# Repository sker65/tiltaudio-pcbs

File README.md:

# tiltaudio-pcbs
PCBs and shields for TILT!Audio, see https://tiltaudio.com

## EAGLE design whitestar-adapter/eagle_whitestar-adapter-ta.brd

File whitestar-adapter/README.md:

# Whitestar Adapter

Small PCB to hook on the main cpu to connect TILT!Audio with Whitestar mainboards

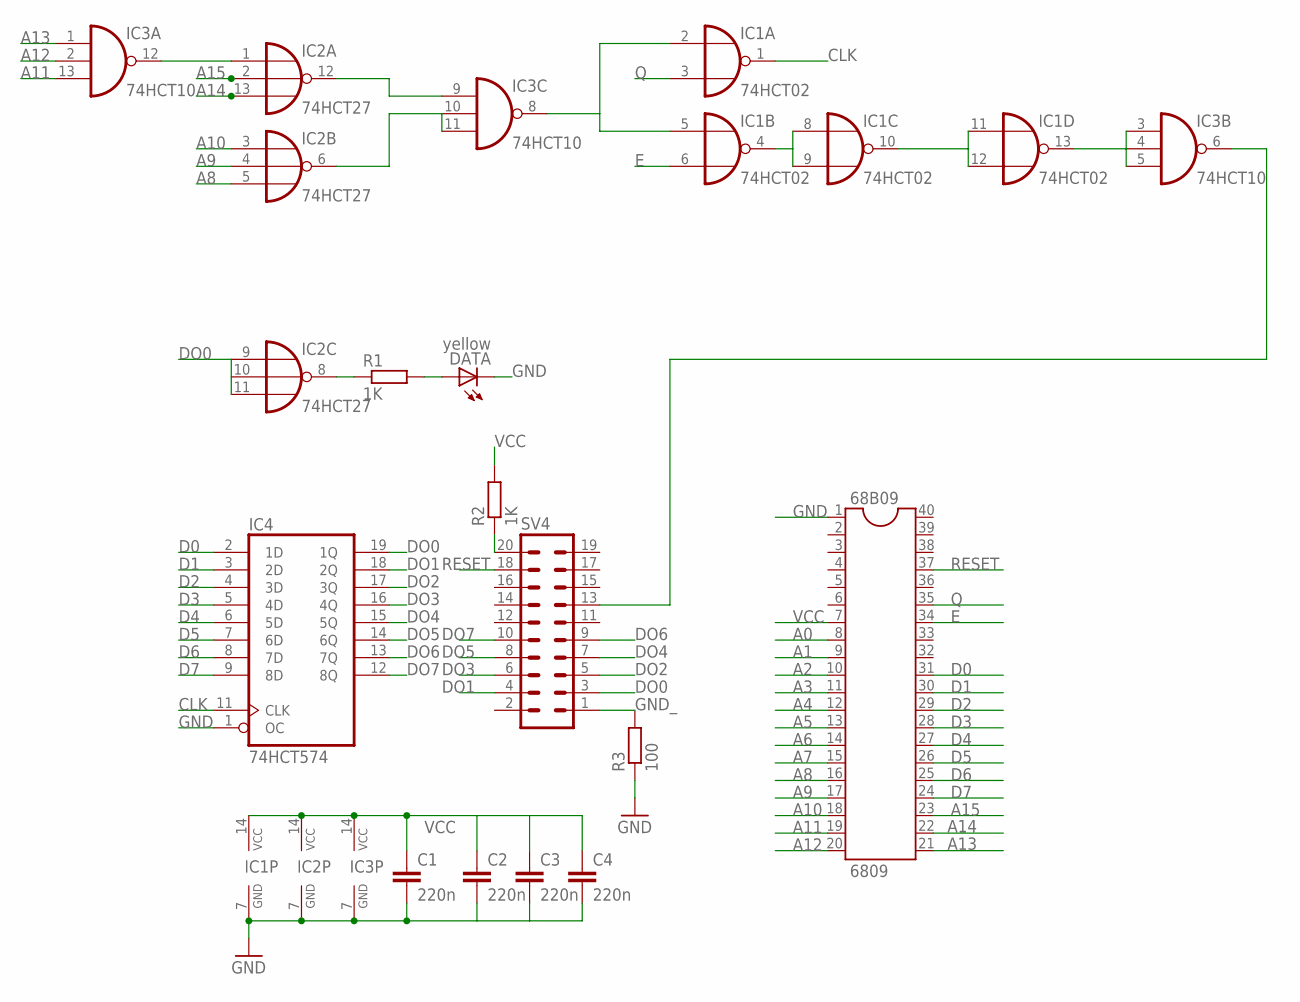
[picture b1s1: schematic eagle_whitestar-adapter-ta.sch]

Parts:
68B09: 6809; DIL40
C1, C2, C3, C4: 220n; C0603K
DATA: yellow; SML0603
IC1: 74HCT02; SO14
IC2: 74HCT27; SO14
IC3: 74HCT10; SO14
IC4: 74HCT574; SO20W
R1, R2: 1K; R0603
R3: 100; R0603
SV4: MA10-2

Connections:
A0: 68B09.8
A1: 68B09.9
A2: 68B09.10
A3: 68B09.11
A4: 68B09.12
A5: 68B09.13
A6: 68B09.14
A7: 68B09.15
A8: 68B09.16, IC2.5 (I2)
A9: 68B09.17, IC2.4 (I1)
A10: 68B09.18, IC2.3 (I0)
A11: 68B09.19, IC3.13 (I2)
A12: 68B09.20, IC3.2 (I1)
A13: 68B09.21, IC3.1 (I0)
A14: 68B09.22, IC2.13 (I2)
A15: 68B09.23, IC2.2 (I1)
CLK: IC1.1 (O), IC4.11 (CLK)
D0: 68B09.31, IC4.2 (1D)
D1: 68B09.30, IC4.3 (2D)
D2: 68B09.29, IC4.4 (3D)
D3: 68B09.28, IC4.5 (4D)
D4: 68B09.27, IC4.6 (5D)
D5: 68B09.26, IC4.7 (6D)
D6: 68B09.25, IC4.8 (7D)
D7: 68B09.24, IC4.9 (8D)
DO0: IC2.9 (I0), IC2.10 (I1), IC2.11 (I2), IC4.19 (1Q), SV4.3
DO1: IC4.18 (2Q), SV4.4
DO2: IC4.17 (3Q), SV4.5
DO3: IC4.16 (4Q), SV4.6
DO4: IC4.15 (5Q), SV4.7
DO5: IC4.14 (6Q), SV4.8
DO6: IC4.13 (7Q), SV4.9
DO7: IC4.12 (8Q), SV4.10
E: 68B09.34, IC1.6 (I1)
GND: 68B09.1, C1.2, C2.2, C3.2, C4.2, DATA.C, IC1.7 (GND), IC2.7 (GND), IC3.7 (GND), IC4.1 (OC), IC4.10 (GND), R3.1
GND_: R3.2, SV4.1
unnamed: IC2.1 (I0), IC3.12 (O)
unnamed: IC2.12 (O), IC3.9 (I0)
unnamed: IC2.6 (O), IC3.10 (I1), IC3.11 (I2)
unnamed: IC1.2 (I0), IC1.5 (I0), IC3.8 (O)
unnamed: DATA.A, R1.2
unnamed: IC1.4 (O), IC1.8 (I0), IC1.9 (I1)
unnamed: IC1.10 (O), IC1.11 (I0), IC1.12 (I1)
unnamed: IC1.13 (O), IC3.3 (I0), IC3.4 (I1), IC3.5 (I2)
unnamed: IC3.6 (O), SV4.13
unnamed: R2.1, SV4.20
unnamed: IC2.8 (O), R1.1
Q: 68B09.35, IC1.3 (I1)
RESET: 68B09.37, SV4.18
VCC: 68B09.7, C1.1, C2.1, C3.1, C4.1, IC1.14 (VCC), IC2.14 (VCC), IC3.14 (VCC), IC4.20 (VCC), R2.2

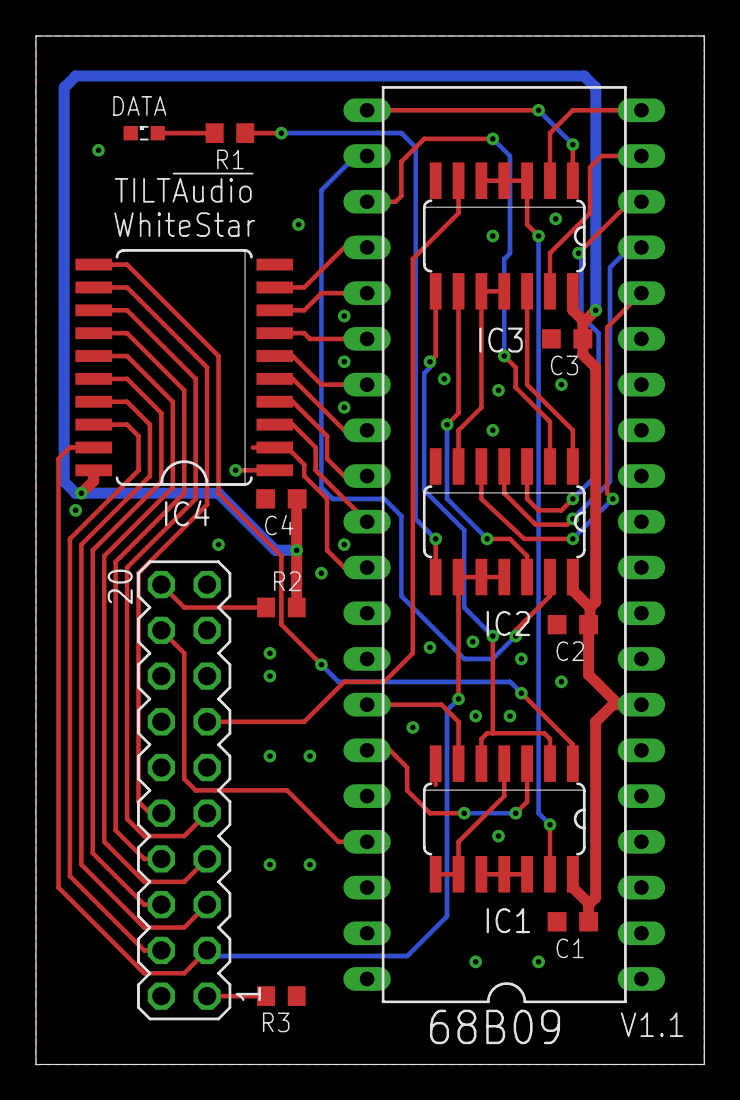
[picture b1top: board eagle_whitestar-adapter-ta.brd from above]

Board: 2 copper layers, 37.1 x 57.1 mm, 14 parts (0 on the bottom side), 42 nets.

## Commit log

2021-10-03 - initial
2021-10-03 - img as html markup
